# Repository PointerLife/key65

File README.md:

# key65
It is a 65 key layout, mechanical keyboard!  

## PCB
| Schematics |
| --- |
| | 
| | 

| PCB |
| --- |
|  |

## Case
The case is divided into two parts front and back for easy installation and some design experiments. 
| Case front part|
| --- |
|  |
|  |

| Case bottom part|
| --- |
|  |

## Layout
| Layout |
| --- |
|  |

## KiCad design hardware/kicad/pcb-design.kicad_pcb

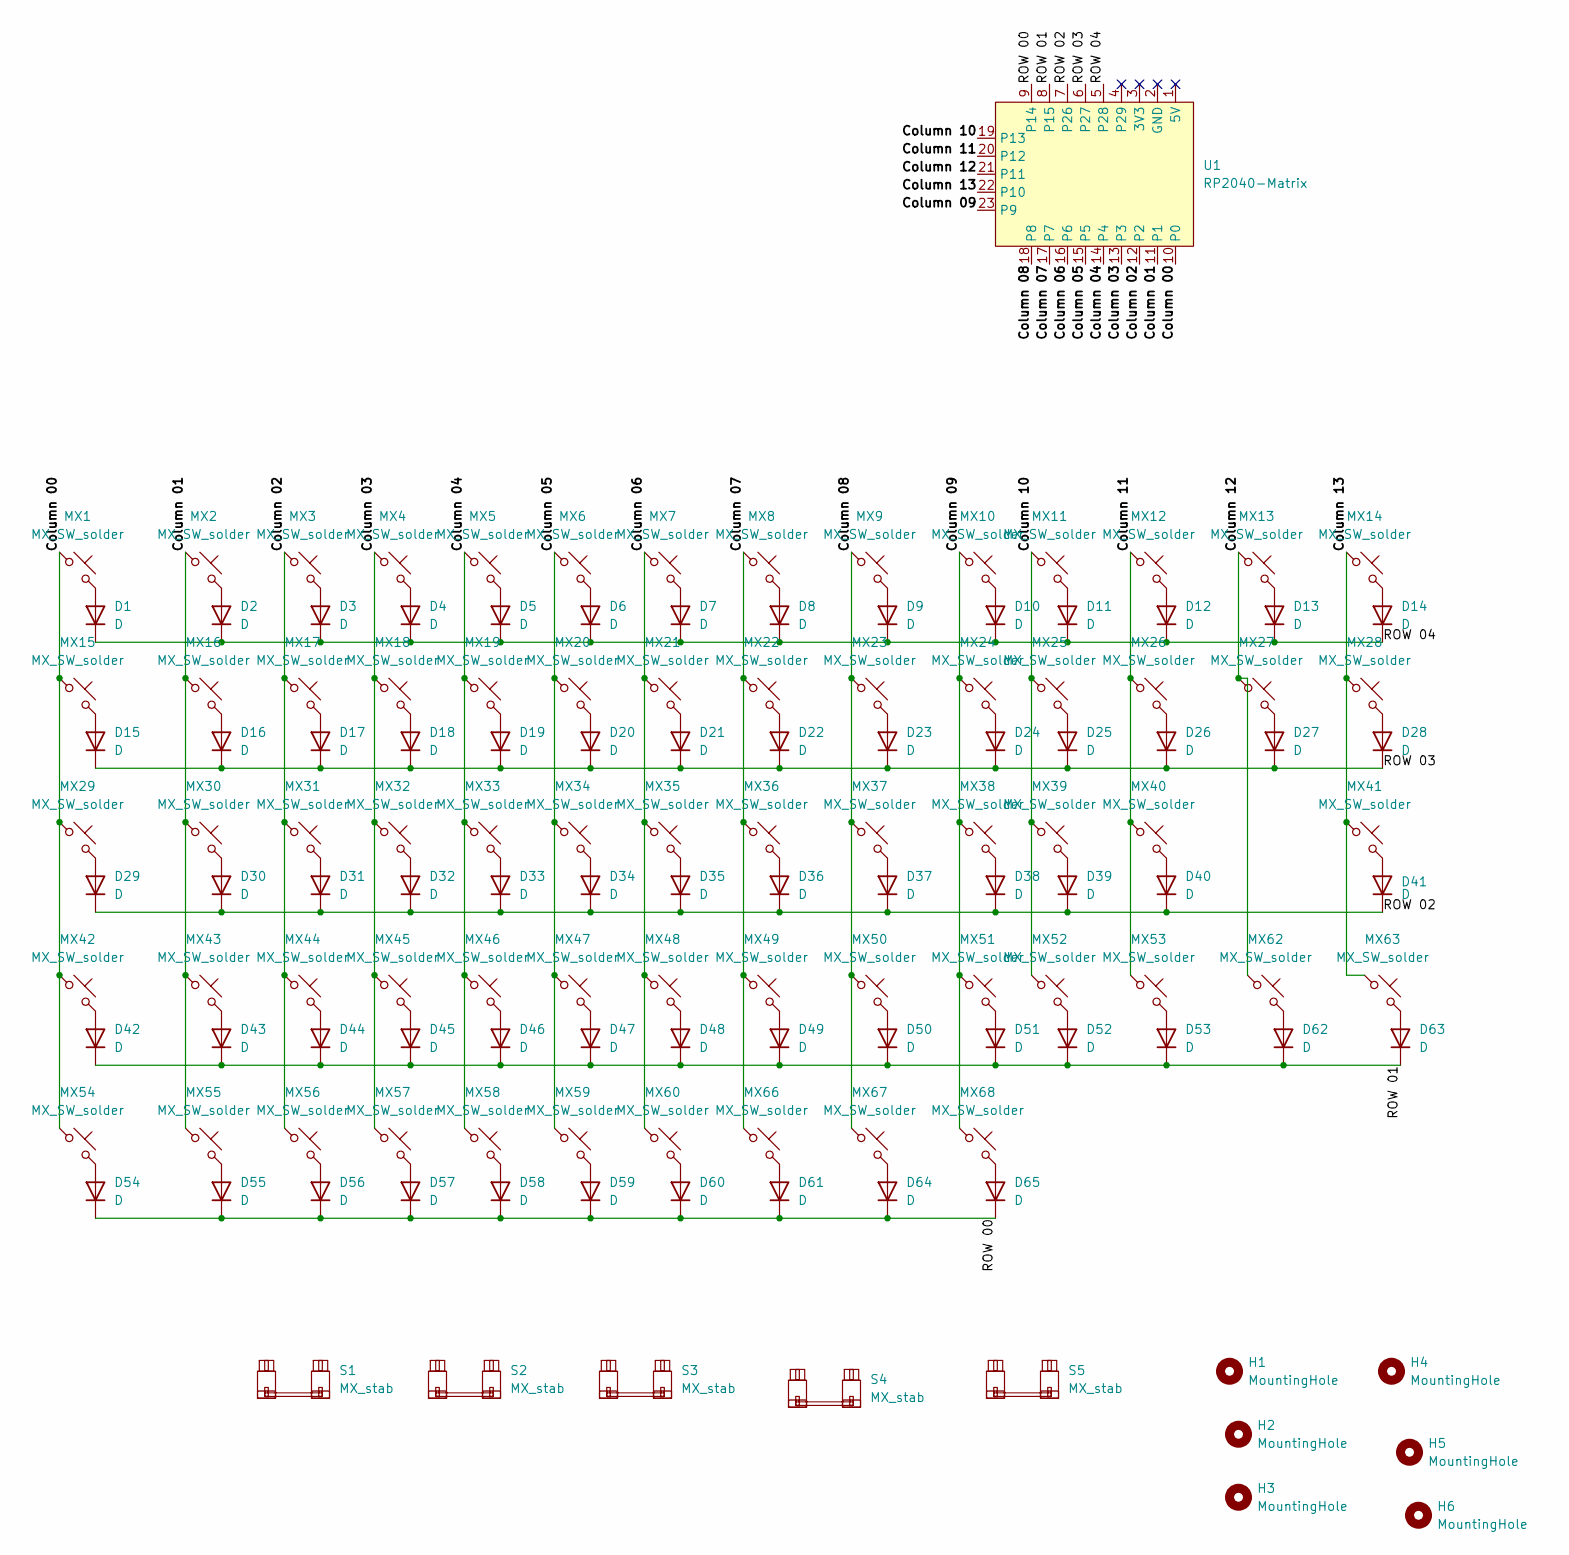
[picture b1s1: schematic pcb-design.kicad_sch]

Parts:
D1, D2, D3, D4, D5, D6, D7, D8, D9, D10, D11, D12, D13, D14, D15, D16, D17, D18, D19, D20, D21, D22, D23, D24, D25, D26, D27, D28, D29, D30, D31, D32, D33, D34, D35, D36, D37, D38, D39, D40, D41, D42, D43, D44, D45, D46, D47, D48, D49, D50, D51, D52, D53, D54, D55, D56, D57, D58, D59, D60, D61, D62, D63, D64, D65: D; D_DO-35_SOD27_P10.16mm_Horizontal
H1, H2, H3, H4, H5, H6: MountingHole; MountingHole_2.2mm_M2
MX1, MX2, MX3, MX4, MX5, MX6, MX7, MX8, MX9, MX10, MX11, MX12, MX13, MX14, MX16, MX17, MX18, MX19, MX20, MX21, MX22, MX23, MX24, MX25, MX26, MX27, MX30, MX31, MX32, MX33, MX34, MX35, MX36, MX37, MX38, MX39, MX40, MX41, MX42, MX43, MX44, MX45, MX46, MX47, MX48, MX49, MX50, MX51, MX52, MX53, MX55, MX57, MX62, MX63, MX66, MX67, MX68: MX_SW_solder; SW_MX_1u
MX15, MX28: MX_SW_solder; SW_MX_1.5u
MX29: MX_SW_solder; SW_MX_1.75u
MX54, MX56, MX58, MX59, MX60: MX_SW_solder; SW_MX_1.25u
S1: MX_stab; STAB_MX_P_2u
S2, S3, S4: MX_stab; STAB_MX_P_2.25u
S5: MX_stab; STAB_MX_P_6.25u
U1: RP2040-Matrix; RP2040-Matrix_AC

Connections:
/Column 00: MX1.1, MX15.1, MX29.1, MX42.1, MX54.1, U1.10 (P0)
/Column 01: MX2.1, MX16.1, MX30.1, MX43.1, MX55.1, U1.11 (P1)
/Column 02: MX3.1, MX17.1, MX31.1, MX44.1, MX56.1, U1.12 (P2)
/Column 03: MX4.1, MX18.1, MX32.1, MX45.1, MX57.1, U1.13 (P3)
/Column 04: MX5.1, MX19.1, MX33.1, MX46.1, MX58.1, U1.14 (P4)
/Column 05: MX6.1, MX20.1, MX34.1, MX47.1, MX59.1, U1.15 (P5)
/Column 06: MX7.1, MX21.1, MX35.1, MX48.1, MX60.1, U1.16 (P6)
/Column 07: MX8.1, MX22.1, MX36.1, MX49.1, MX66.1, U1.17 (P7)
/Column 08: MX9.1, MX23.1, MX37.1, MX50.1, MX67.1, U1.18 (P8)
/Column 09: MX10.1, MX24.1, MX38.1, MX51.1, MX68.1, U1.23 (P9)
/Column 10: MX11.1, MX25.1, MX39.1, MX52.1, U1.19 (P13)
/Column 11: MX12.1, MX26.1, MX40.1, MX53.1, U1.20 (P12)
/Column 12: MX13.1, MX27.1, MX62.1, U1.21 (P11)
/Column 13: MX14.1, MX28.1, MX41.1, MX63.1, U1.22 (P10)
/ROW 00: D54.1 (K), D55.1 (K), D56.1 (K), D57.1 (K), D58.1 (K), D59.1 (K), D60.1 (K), D61.1 (K), D64.1 (K), D65.1 (K), U1.9 (P14)
/ROW 01: D42.1 (K), D43.1 (K), D44.1 (K), D45.1 (K), D46.1 (K), D47.1 (K), D48.1 (K), D49.1 (K), D50.1 (K), D51.1 (K), D52.1 (K), D53.1 (K), D62.1 (K), D63.1 (K), U1.8 (P15)
/ROW 02: D29.1 (K), D30.1 (K), D31.1 (K), D32.1 (K), D33.1 (K), D34.1 (K), D35.1 (K), D36.1 (K), D37.1 (K), D38.1 (K), D39.1 (K), D40.1 (K), D41.1 (K), U1.7 (P26)
/ROW 03: D15.1 (K), D16.1 (K), D17.1 (K), D18.1 (K), D19.1 (K), D20.1 (K), D21.1 (K), D22.1 (K), D23.1 (K), D24.1 (K), D25.1 (K), D26.1 (K), D27.1 (K), D28.1 (K), U1.6 (P27)
/ROW 04: D1.1 (K), D2.1 (K), D3.1 (K), D4.1 (K), D5.1 (K), D6.1 (K), D7.1 (K), D8.1 (K), D9.1 (K), D10.1 (K), D11.1 (K), D12.1 (K), D13.1 (K), D14.1 (K), U1.5 (P28)
unnamed: D1.2 (A), MX1.2
unnamed: D2.2 (A), MX2.2
unnamed: D3.2 (A), MX3.2
unnamed: D4.2 (A), MX4.2
unnamed: D5.2 (A), MX5.2
unnamed: D6.2 (A), MX6.2
unnamed: D7.2 (A), MX7.2
unnamed: D8.2 (A), MX8.2
unnamed: D9.2 (A), MX9.2
unnamed: D10.2 (A), MX10.2
unnamed: D11.2 (A), MX11.2
unnamed: D12.2 (A), MX12.2
unnamed: D13.2 (A), MX13.2
unnamed: D14.2 (A), MX14.2
unnamed: D15.2 (A), MX15.2
unnamed: D16.2 (A), MX16.2
unnamed: D17.2 (A), MX17.2
unnamed: D18.2 (A), MX18.2
unnamed: D19.2 (A), MX19.2
unnamed: D20.2 (A), MX20.2
unnamed: D21.2 (A), MX21.2
unnamed: D22.2 (A), MX22.2
unnamed: D23.2 (A), MX23.2
unnamed: D24.2 (A), MX24.2
unnamed: D25.2 (A), MX25.2
unnamed: D26.2 (A), MX26.2
unnamed: D27.2 (A), MX27.2
unnamed: D28.2 (A), MX28.2
unnamed: D29.2 (A), MX29.2
unnamed: D30.2 (A), MX30.2
unnamed: D31.2 (A), MX31.2
unnamed: D32.2 (A), MX32.2
unnamed: D33.2 (A), MX33.2
unnamed: D34.2 (A), MX34.2
unnamed: D35.2 (A), MX35.2
unnamed: D36.2 (A), MX36.2
unnamed: D37.2 (A), MX37.2
unnamed: D38.2 (A), MX38.2
unnamed: D39.2 (A), MX39.2
unnamed: D40.2 (A), MX40.2
unnamed: D41.2 (A), MX41.2
unnamed: D42.2 (A), MX42.2
unnamed: D43.2 (A), MX43.2
unnamed: D44.2 (A), MX44.2
unnamed: D45.2 (A), MX45.2
unnamed: D46.2 (A), MX46.2
unnamed: D47.2 (A), MX47.2
unnamed: D48.2 (A), MX48.2
unnamed: D49.2 (A), MX49.2
unnamed: D50.2 (A), MX50.2
unnamed: D51.2 (A), MX51.2
unnamed: D52.2 (A), MX52.2
unnamed: D53.2 (A), MX53.2
unnamed: D54.2 (A), MX54.2
unnamed: D55.2 (A), MX55.2
unnamed: D56.2 (A), MX56.2
unnamed: D57.2 (A), MX57.2
unnamed: D58.2 (A), MX58.2
unnamed: D59.2 (A), MX59.2
unnamed: D60.2 (A), MX60.2
unnamed: D61.2 (A), MX66.2
unnamed: D62.2 (A), MX62.2
unnamed: D63.2 (A), MX63.2
unnamed: D64.2 (A), MX67.2
unnamed: D65.2 (A), MX68.2

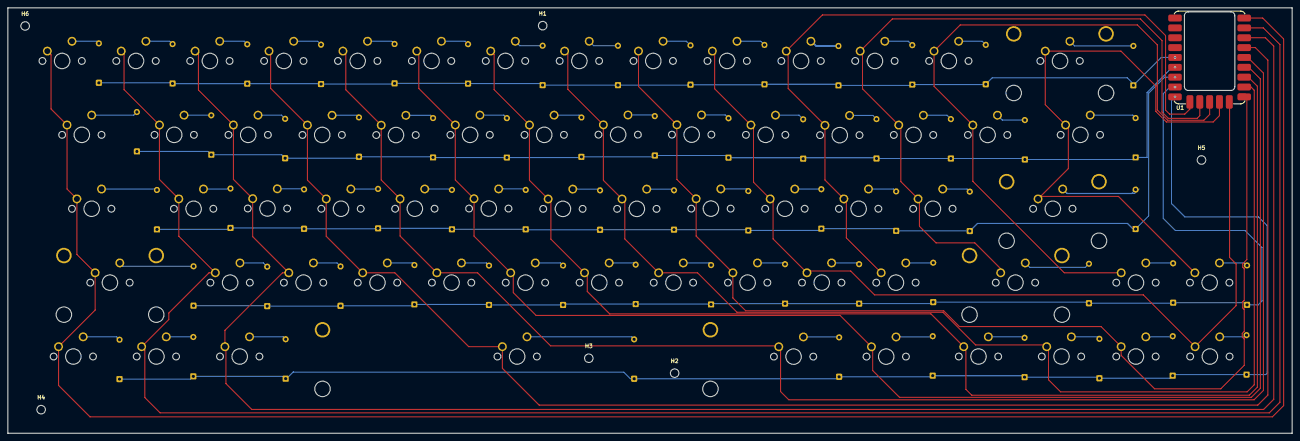
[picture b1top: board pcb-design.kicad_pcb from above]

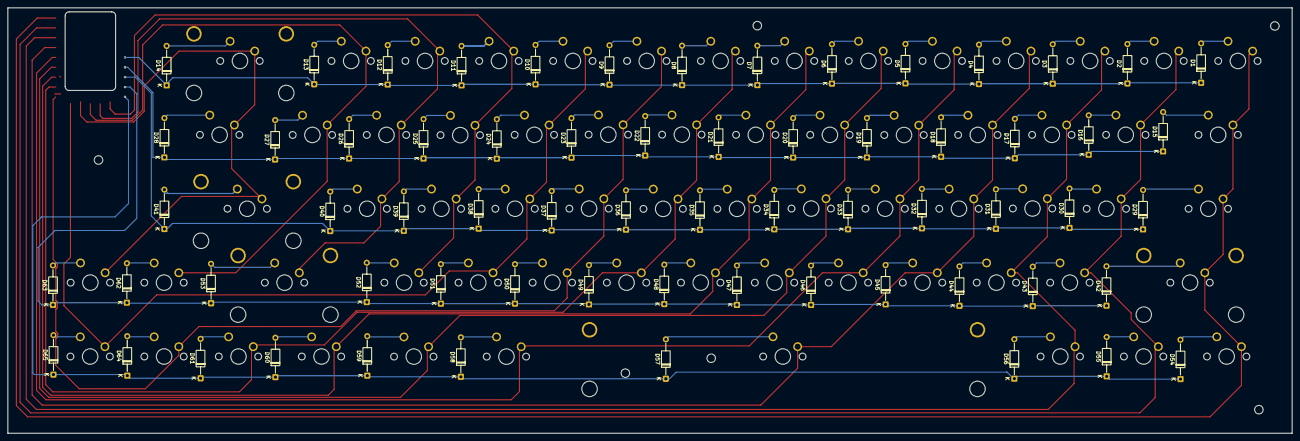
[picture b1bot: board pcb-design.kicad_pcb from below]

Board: 2 copper layers, 331.1 x 109.7 mm, 142 parts (65 on the bottom side), 84 nets.

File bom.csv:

"Id";"Designator";"Footprint";"Quantity";"Designation";"Supplier and ref";
1;"D1, D2, D3, D4, D5, D6, D7, D8, D9, D10, D11, D12, D13, D14, D15, D16, D17, D18, D19, D20, D21, D22, D23, D24, D25, D26, D27, D28, D29, D30, D31, D32, D33, D34, D35, D36, D37, D38, D39, D40, D41, D42, D43, D44, D45, D46, D47, D48, D49, D50, D51, D52, D53, D54, D55, D56, D57, D58, D59, D60, D61, D62, D63, D64, D65";"D_DO-35_SOD27_P10.16mm_Horizontal";65;"D";;;
2;"MX1, MX2, MX3, MX4, MX5, MX6, MX7, MX8, MX9, MX10, MX11, MX12, MX13, MX14, MX16, MX17, MX18, MX19, MX20, MX21, MX22, MX23, MX24, MX25, MX26, MX27, MX30, MX31, MX32, MX33, MX34, MX35, MX36, MX37, MX38, MX39, MX40, MX41, MX42, MX43, MX44, MX45, MX46, MX47, MX48, MX49, MX50, MX51, MX52, MX53, MX55, MX57, MX62, MX63, MX66, MX67, MX68";"SW_MX_1u";57;"MX_SW_solder";;;
3;"MX15, MX28";"SW_MX_1.5u";2;"MX_SW_solder";;;
4;"MX29";"SW_MX_1.75u";1;"MX_SW_solder";;;
5;"MX54, MX56, MX58, MX59, MX60";"SW_MX_1.25u";5;"MX_SW_solder";;;
6;"S1";"STAB_MX_P_2u";1;"MX_stab";;;
7;"S2, S3, S4";"STAB_MX_P_2.25u";3;"MX_stab";;;
8;"S5";"STAB_MX_P_6.25u";1;"MX_stab";;;
